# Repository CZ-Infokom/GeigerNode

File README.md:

# GeigerNode

Bare-metal firmware for the GeigerNode PCB: an ATmega328PB that runs an SBM-20 Geiger tube. The I2C map is chosen at compile time: `make PROTOCOL=native` is protocol v1 at `0x67`; `make PROTOCOL=radsens` is the ClimateGuard RadSens slave at `0x66`.

This board generates about 400 V. Stay clear of the HV section when the LED is on after reset, and after `make flash`. The programmer reset holds the LED on for 500 ms, then 380 V starts.

## Current image

- Tube: SBM-20
- Native protocol v2 at `0x67`: device ID `0x474E`, firmware `0.2.1`, CPM × 10 and nSv/h. Default window 300 s, ceiling 400 s. Calibration Q16.16 `604948` (65 impulses/µR as nSv/h per CPM). Window, holdoff, peak span, and calibration are writable. The peak span is 10..60 s, default 10. `0x40`/`0x48` are the busiest slice still in the dose window, and `0x44`/`0x4C` are the latched slice, which a full read of either register clears. Write `01` at `0x38` to clear the histogram; a holdoff write also clears it. A peak-span write clears both peaks.
- RadSens image at `0x66`: firmware byte `0x01` is `0x04`, sensitivity default 65 impulses/µR, static window fixed at 300 s
- I2C: hardware TWI0. Bit-bang fallback is `fallback/bitbang-i2c`.
- Operating point: 380 V at 2400 Hz, 100 µs pulse cap, production abort around 400 V
- Holdoff: default 200 µs, native range 0..300 µs. Pulse counting does not scale by S.
- Host: Meshtastic reads native `0x04`..`0x0B`. RadSens masters need `PROTOCOL=radsens`.

The JNA DR-M3 comparison has not been run. Do not replace 65 until that measurement is accepted.

## Repository layout

| Path | What it is |
| --- | --- |
| [`firmware/`](firmware/) | AVR sources, Makefile, and flash targets |
| [`firmware/flipper/`](firmware/flipper/) | Flash-only Intel HEX images for the Flipper AVR Flasher |
| [`hardware/`](hardware/) | KiCad 10 rev A board. `hardware/production/` is the 2026-09-17 fab export |
| [`firmware/geigernode-i2c-protocol.md`](firmware/geigernode-i2c-protocol.md) | Native I2C protocol v1 |
| [`firmware/i2c-register-map.md`](firmware/i2c-register-map.md) | RadSens register map |
| [`firmware/bringup/README.md`](firmware/bringup/README.md) | Bring-up log and host toolchain |
| [`GeigerNode Firmware Development.md`](GeigerNode%20Firmware%20Development.md) | Development plan and PROJECT STATUS |

## Build and flash

From `firmware/`:

```sh
make PROTOCOL=native
make PROTOCOL=native flash
make PROTOCOL=native verify
```

The board is externally powered. Atmel-ICE does not power the target. `make flash` programs flash only and chip-erases EEPROM. Do not write fuses unless a human has approved the bytes. Details are in [`firmware/README.md`](firmware/README.md).

## Branches

| Branch | Role |
| --- | --- |
| `feature/*` | New work |
| `dev` | Integration |
| `master` | Tagged releases only |

Release path: `feature/*` → `dev` → `master` with a `vMAJOR.MINOR.PATCH` tag.

## Continuous integration

[`.github/workflows/firmware.yml`](.github/workflows/firmware.yml) lints and tests pull requests and pushes to `dev` and `master`, then builds both firmware images. The compiler is the AVR 8-bit GNU Toolchain 4.0.0 (`avr-gcc` 15.1.0), and the build treats warnings as errors.

Pushing a version tag publishes a GitHub release. The assets are the native and RadSens Intel HEX images plus the matching Flipper AVR Flasher descriptors:

| Asset | What it is |
| --- | --- |
| `GeigerNode-<tag>-native_flash.hex` | Native protocol at `0x67`. Flash data records and an end record. |
| `GeigerNode-<tag>-native.avr` | Flipper descriptor for that HEX file. |
| `GeigerNode-<tag>-radsens_flash.hex` | RadSens protocol at `0x66`. Flash data records and an end record. |
| `GeigerNode-<tag>-radsens.avr` | Flipper descriptor for that HEX file. |

`v1.2.3` is a release. A tag with a pre-release suffix is a GitHub pre-release and is not marked Latest. That suffix is the SemVer pre-release identifier: `-beta`, `-rc`, `-pre`, `-alpha`, and any other `-identifier`, including dotted forms such as `v0.2.1-beta.2` and `v0.2.0-pre.1`.

Each `.avr` descriptor names the approved fuses LFUSE `E2`, HFUSE `D9`, EFUSE `F5`, and lock `FF`. Flash AVR writes those bytes and chip-erases EEPROM. Do not change those bytes. After the programmer reset the LED is on for 500 ms, then 380 V starts. Stay clear of the HV section. The workflow itself only uploads files.

## Source

Private repository: [CZ-Infokom/GeigerNode](https://github.com/CZ-Infokom/GeigerNode)

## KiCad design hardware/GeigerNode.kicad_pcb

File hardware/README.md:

# GeigerNode hardware

KiCad 10 project for PCB rev A. Open `GeigerNode.kicad_pro`. Symbols and footprints are stored in the schematic and board. 3D models resolve through `${KICAD10_3DMODEL_DIR}`.

`production/` is the fabrication export from 2026-09-17: `GeigerNode_A.zip` (Gerbers and drills), `bom.csv`, `positions.csv`, `designators.csv`, and `netlist.ipc`. The schematic and board files were saved a few minutes after that export. Regenerate this directory before the next fab order.

KiCad automatic backups and `GeigerNode.kicad_prl` are gitignored.

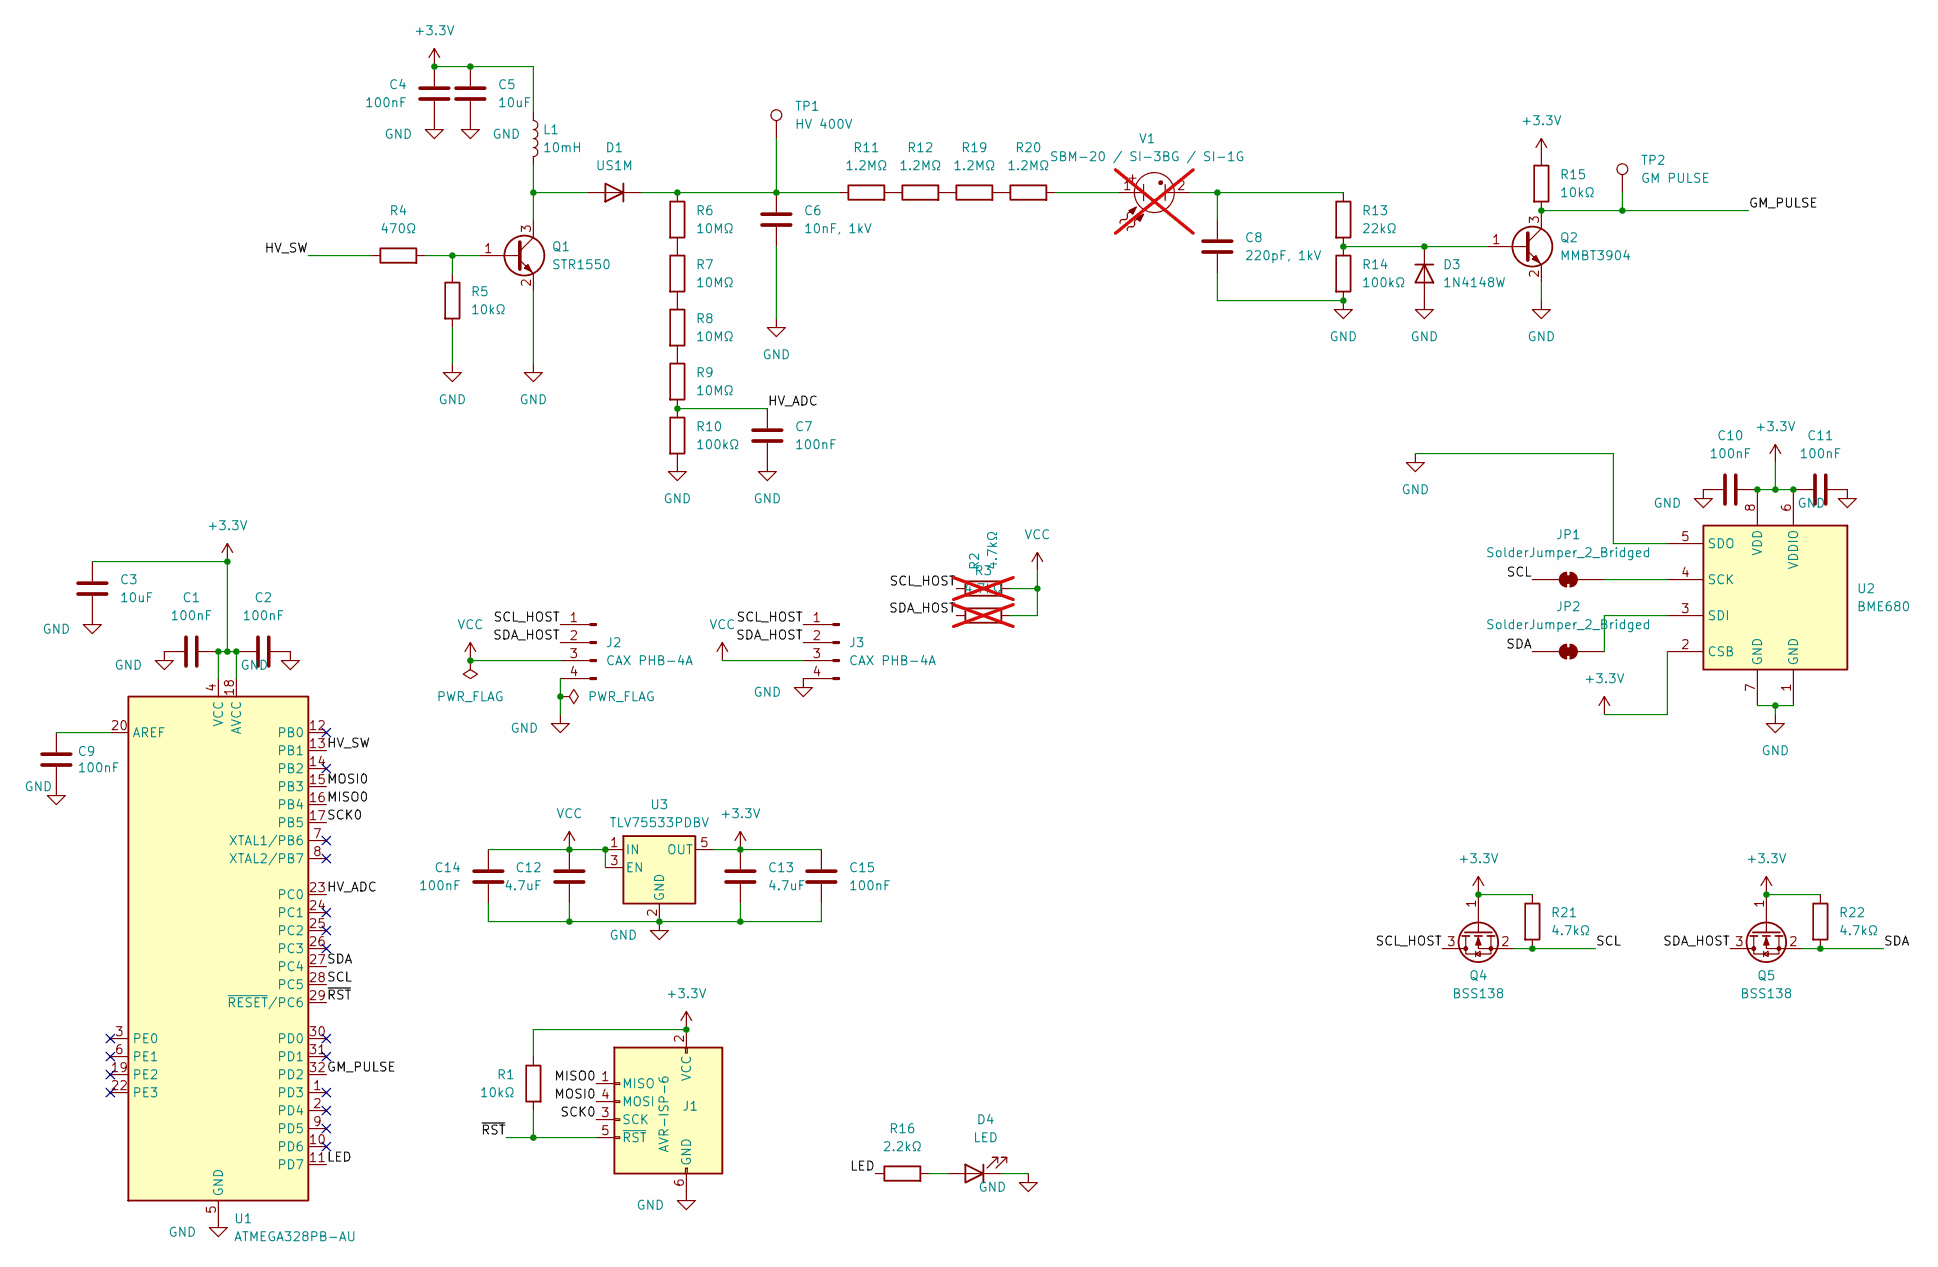
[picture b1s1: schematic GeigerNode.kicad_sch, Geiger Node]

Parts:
C1, C2, C4, C7, C9, C10, C11: 100nF; C_0805_2012Metric
C3: 10uF; C_1206_3216Metric
C5: 10uF; C_0805_2012Metric
C6: 10nF, 1kV; C_1206_3216Metric; JLC C344191
C8: 220pF, 1kV; C_1206_3216Metric; JLC C22374883
C12, C13: 4.7uF; C_0805_2012Metric; JLC C415536
C14, C15: 100nF; C_0805_2012Metric; JLC C396717
D1: US1M; D_SMA; JLC C22448038
D3: 1N4148W; D_SOD-123; JLC C115103
D4: LED; D_0805_2012Metric
J1: AVR-ISP-6; Tag-Connect_TC2030-IDC-FP_2x03_P1.27mm_Vertical
J2, J3: CAX PHB-4A; JST_PH_B4B-PH-K_1x04_P2.00mm_Vertical; JLC C2847689
JP1, JP2: SolderJumper_2_Bridged; SolderJumper-2_P1.3mm_Bridged_RoundedPad1.0x1.5mm
L1: 10mH; L_12x12mm_H4.5mm; JLC C718296
Q1: STR1550; SOT-23; JLC C907714
Q2: MMBT3904; SOT-23; JLC C280057
Q4, Q5: BSS138; SOT-23; JLC C52895
R1, R5, R15: 10kΩ; R_0805_2012Metric
R2, R3: 4.7kΩ; R_0805_2012Metric; not fitted
R4: 470Ω; R_0805_2012Metric
R6, R7, R8, R9: 10MΩ; R_1206_3216Metric; JLC C326960
R10, R14: 100kΩ; R_0805_2012Metric
R11, R12, R19, R20: 1.2MΩ; R_1206_3216Metric; JLC C2889803
R13: 22kΩ; R_0805_2012Metric
R16: 2.2kΩ; R_0805_2012Metric
R21, R22: 4.7kΩ; R_0805_2012Metric
TP1: HV 400V; TestPoint_Pad_D2.0mm
TP2: GM PULSE; TestPoint_Pad_D2.0mm
U1: ATMEGA328PB-AU; TQFP-32_7x7mm_P0.8mm; JLC C132230
U2: BME680; Bosch_LGA-8_3x3mm_P0.8mm_ClockwisePinNumbering; JLC C125972
U3: TLV75533PDBV; SOT-23-5; JLC C404027
V1: SBM-20 / SI-3BG / SI-1G; SBM-20; not fitted

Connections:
+3.3V: C1.2, C2.1, C3.1, C4.1, C5.1, C10.2, C11.1, C13.1, C15.1, J1.2 (VCC), L1.1, Q4.1 (G), Q5.1 (G), R1.1, R15.1, R21.1, R22.1, U1.4 (VCC), U1.18 (AVCC), U2.2 (CSB), U2.6 (VDDIO), U2.8 (VDD), U3.5 (OUT)
/GM_PULSE: Q2.3 (C), R15.2, TP2.1 (1_1), U1.32 (PD2)
/HV_ADC: C7.1, R9.2, R10.1, U1.23 (PC0)
/HV_SW: R4.1, U1.13 (PB1)
/LED: R16.1, U1.11 (PD7)
/MISO0: J1.1 (MISO), U1.16 (PB4)
/MOSI0: J1.4 (MOSI), U1.15 (PB3)
/SCK0: J1.3 (SCK), U1.17 (PB5)
/SCL: JP1.1 (A), Q4.2 (S), R21.2, U1.28 (PC5)
/SCL_HOST: J2.1, J3.1, Q4.3 (D), R2.1
/SDA: JP2.1 (A), Q5.2 (S), R22.2, U1.27 (PC4)
/SDA_HOST: J2.2, J3.2, Q5.3 (D), R3.1
/~RST: J1.5 (~RST), R1.2, U1.29 (~RESET/PC6)
GND: C1.1, C2.2, C3.2, C4.2, C5.2, C6.2, C7.2, C8.2, C9.2, C10.1, C11.2, C12.2, C13.2, C14.2, C15.2, D3.2 (A), D4.1 (K), J1.6 (GND), J2.4, J3.4, Q1.2 (E), Q2.2 (E), R5.2, R10.2, R14.2, U1.5 (GND), U1.21 (GND), U2.1 (GND), U2.5 (SDO), U2.7 (GND), U3.2 (GND)
unnamed: C8.1, R13.1, V1.2
unnamed: D1.2 (A), L1.2, Q1.3 (C)
unnamed: C6.1, D1.1 (K), R6.1, R11.1, TP1.1 (1_1)
unnamed: D3.1 (K), Q2.1 (B), R13.2, R14.1
unnamed: D4.2 (A), R16.2
unnamed: JP1.2 (B), U2.4 (SCK)
unnamed: JP2.2 (B), U2.3 (SDI)
unnamed: Q1.1 (B), R4.2, R5.1
unnamed: R6.2, R7.1
unnamed: R7.2, R8.1
unnamed: R8.2, R9.1
unnamed: R11.2, R12.1
unnamed: R12.2, R19.1
unnamed: R19.2, R20.1
unnamed: R20.2, V1.1
unnamed: C9.1, U1.20 (AREF)
VCC: C12.1, C14.1, J2.3, J3.3, R2.2, R3.2, U3.1 (IN), U3.3 (EN)

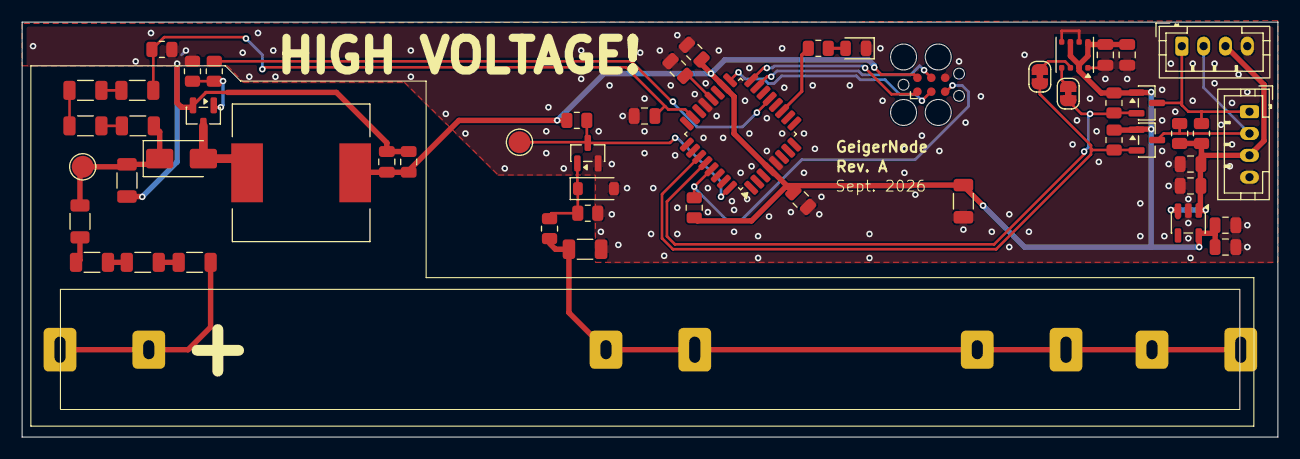
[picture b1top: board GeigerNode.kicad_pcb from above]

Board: 2 copper layers, 115.0 x 38.0 mm, 54 parts (0 on the bottom side), 31 nets.

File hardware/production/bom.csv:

Designator,Footprint,Quantity,Value,LCSC Part #
"C1, C10, C11, C2, C4, C7, C9",0805,7,100nF,
"C12, C13",0805,2,4.7uF,C415536
"C14, C15",0805,2,100nF,C396717
C3,1206,1,10uF,
C5,0805,1,10uF,
C6,1206,1,"10nF, 1kV",C344191
C8,1206,1,"220pF, 1kV",C22374883
D1,D_SMA,1,US1M,C22448038
D3,D_SOD-123,1,1N4148W,C115103
D4,0805,1,LED,
J1,Tag-Connect_TC2030-IDC-FP_2x03_P1.27mm_Vertical,1,AVR-ISP-6,
"J2, J3",JST_PH_B4B-PH-K_1x04_P2.00mm_Vertical,2,CAX PHB-4A,C2847689
L1,L_12x12mm_H4.5mm,1,10mH,C718296
Q1,SOT-23,1,STR1550,C907714
Q2,SOT-23,1,MMBT3904,C280057
"Q4, Q5",SOT-23,2,BSS138,C52895
"R1, R15, R5",0805,3,10kΩ,
"R10, R14",0805,2,100kΩ,
"R11, R12, R19, R20",1206,4,1.2MΩ,C2889803
R13,0805,1,22kΩ,
R16,0805,1,2.2kΩ,
"R2, R21, R22, R3",0805,4,4.7kΩ,
R4,0805,1,470Ω,
"R6, R7, R8, R9",1206,4,10MΩ,C326960
TP1,TestPoint_Pad_D2.0mm,1,HV 400V,
TP2,TestPoint_Pad_D2.0mm,1,GM PULSE,
U1,TQFP-32_7x7mm_P0.8mm,1,ATMEGA328PB-AU,C132230
U2,Bosch_LGA-8_3x3mm_P0.8mm_ClockwisePinNumbering,1,BME680,C125972
U3,SOT-23-5,1,TLV75533PDBV,C404027
V1,SBM-20,1,SBM-20 / SI-3BG / SI-1G,

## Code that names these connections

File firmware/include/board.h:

#ifndef BOARD_H
#define BOARD_H

/*
 * GeigerNode, ATmega328PB-AU, 3.3 V.
 *
 * HV_SW is PB1 / OC1A. It drives the high-voltage converter transistor.
 * gpio_init drives it low before any timer starts. Timer1 then emits the
 * open-loop pulse. Fault and reset disconnect OC1A and leave the pin low.
 *
 * LED is PD7.
 * GM_PULSE is PD2 / INT0, active low, falling edge. The pin is an input with a pull-up.
 * PD3 is spare and stays untouched.
 * HV_ADC is PC0 / ADC0. The default image leaves the converter off while it is read.
 * I2C SDA is PC4 and SCL is PC5. Hardware TWI0 is the slave.
 * PROTOCOL=native answers at 0x67. PROTOCOL=radsens answers at 0x66.
 * Pin-change bit-bang is off. The bit-banged image is on
 * branch fallback/bitbang-i2c.
 * Timer2 is the millisecond tick. Its pin outputs stay disconnected.
 * Timer1 is the HV pulse. Its hard maximum width is 100 us.
 * Every reset waits 500 ms, then regulates 380 V at 2400 Hz. There is
 * no arm word. The native map is read-only. A RadSens host can stop or
 * start the generator and can store a new address and sensitivity.
 * Pulse width stays at or below 100 us. A fault forces PB1 low. An
 * operational fault may start again after a cooldown; an illegal pulse
 * or rate, or a spent budget, stays off until a RadSens host writes 1
 * or the native image is reset. During the 500 ms wait the LED is on.
 * During RUN it flashes on for each GM pulse.
 */

#define HV_SW_PORT     PORTB
#define HV_SW_DDR      DDRB
#define HV_SW_PORT_BIT PORTB1
#define HV_SW_DDR_BIT  DDB1

#define LED_PORT       PORTD
#define LED_DDR        DDRD
#define LED_PORT_BIT   PORTD7
#define LED_DDR_BIT    DDD7

#define GM_PULSE_DDR      DDRD
#define GM_PULSE_PORT     PORTD
#define GM_PULSE_DDR_BIT  DDD2
#define GM_PULSE_PORT_BIT PORTD2

#define I2C_SDA_DDR       DDRC
#define I2C_SDA_PORT      PORTC
#define I2C_SDA_PIN       PINC
#define I2C_SDA_BIT       PC4
#define I2C_SCL_DDR       DDRC
#define I2C_SCL_PORT      PORTC
#define I2C_SCL_PIN       PINC
#define I2C_SCL_BIT       PC5

#endif
